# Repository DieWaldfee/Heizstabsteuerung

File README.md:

# Heizstabsteuerung

Heizstabsteuerung (Platine und Software) zur Ansteuerung eines Heizstabs in einem Pufferspeicher (Heizung)

**zugehörige Repositories**<br>

- PowerGuard (Steuerungsplatine <a href="https://github.com/DieWaldfee/PowerGuard"> Link </a>)
- Heizstabsteuerung (dieses Repository)
- Heizstab_ioBroker (Ansteuerungs-Blockly - ein MQTT-Broker wird benötigt - Link)

**Funktion:** <br>
Der ESP32 steuert 3 Temperatursensoren (DS18B20) an und liest diese aus. Zwei der Sensoren sollen am Referenzpunkt der Heizungsanlage (an Pufferspeichers der Heizung) angebracht werden, in dem auch der elektrische Heizstab eingeschraubt ist.
Die beiden Werte werden einerseits verglichen und andererseits benutzt, um die Pufferspeichertemperatur zu überwachen. Liegt die Temperatur zu hoch, dann ist zu viel Energie im Pufferspeicher und vermutlich ist der Heizstab dafür ursächlich -> der Heizstabsteuerung abgeschaltet (L1, L2, L3)und damit in den sicheren Zustand überführt.<p>
Liegt die Temperatur der beiden Sensoren über der eingestellten, kritischen Temperatur, so schaltet sich der ESP32 ganz ab und meldet dies optisch über die rote LED. Die Standardschaltung erfolgt über die beiden Sensoren. Eine Fehlerabschaltung erfolgt auch, wenn die Werte der Sensoren zu stark differieren (float deltaT = 2.0;).
Der dritte Sensor wird am höchsten Punkt des Pufferspeichers angebracht und dient der Überwachung der maximal zulässigen Puffertemperatur. Der Sensorwert wird zur Notabschaltung des ESP verwendet, sollte der Puffer signifikat zu heiß werden.
Die Kommunikation mit dem ESP32 wird über WiFi abgewickelt und über das Protokoll MQTT umgesetzt. Es stehen mehrere Befehle zur Verfügung, die ebenfalls via MQTT an den ESP gesendet werden kann. Neben "restart" (führt zu einem Neutstart des ESP32) kann die ganze Konfiguration un der debug-Level angepasst werden. Alle Anpassungen sind nach einem Neustart verlohren, da diese nicht permanet gespeichter werden (aber neue Parameter flashen geht ja fix). Befehle werden unter der MQTT-Hierarchie in folgendem Ort empfangen: "SmartHome/Keller/Heizung/ESP32_Heizstabsteuerung/command" (MQTT_SERIAL_RECEIVER_COMMAND)

**Hardwarevarianten:** <br>
Das Programm unterstützt zwei Hardwarevarianten in einem gemeinsamen Code. Die Auswahl erfolgt über den Parameter `HARDWARE_VERSION` in `src/secrets.h`:

- `HARDWARE_VERSION 1` → V1.0 Lochrasterplatine (OK-LED + ERROR-LED)
- `HARDWARE_VERSION 2` → V2.0 Platinenversion/PCB (OK-LED + MSG-LED + ERROR-LED)

**Entwicklungsumgebungen:** <br>
Die Software für den ESP32 wird mit **PlatformIO** (VSCode-Extension) entwickelt. Compile und Flash sind per Knopfdruck oder über `pio run --target upload` möglich. Die Installation ist sehr einfach und im Netz gut dokumentiert.<br>
Die Platine (PCB) habe ich in Eagle von AutoCAD modelliert. Für Maker gibt es eine kostenfreie Version. Die CAM-Daten (PCB-Produktionsdaten), sowie die BOM (Stückliste) sind ebenfalls aus Eagle ausgegeben.
Eine Übersichtsversion der Platine ist mit Fritzing umgesetzt und enthält auch einige Notizen zur Pinbelegung.<br>

**benötigte Umgebung:** <br>

- ioBroker zur Ansteuerung (geht natürlich auch mit anderen SmartHome-Systemen, solange diese MQTT sprechen können)
- ioBroker MGTT-Adapter
- MQTT-Broker: z.B. mosquitto unter Linux/Debian/Raspian...
- 230V Stromversorgung oder alternativ eine 5V Versorgung über z.B. ein USB-Ladegerät (muss 2 ESP32 sicher versorgen können -> 2A reicht völlig aus) oder über die Schraubklemmen anderweitig versorgt.

### Abhängigkeiten (PlatformIO – platformio.ini):

| Header                | Bibliothek                                                                                                  |
| --------------------- | ----------------------------------------------------------------------------------------------------------- |
| `OneWire.h`           | OneWire git-master (v2.3.7 inkompatibel mit ESP-IDF 5.x; v2.3.8 hat einen Bug – git-master enthält den Fix) |
| `DallasTemperature.h` | DallasTemperature by Miles Burton v4.0.4                                                                    |
| `WiFi.h`              | Arduino / ESP32-Framework                                                                                   |
| `WiFiClient.h`        | Arduino / ESP32-Framework                                                                                   |
| `PubSubClient.h`      | PubSubClient by Nick O'Leary v2.8                                                                           |
| `Wire.h`              | Arduino / ESP32-Framework                                                                                   |
| `LiquidCrystal_I2C.h` | LiquidCrystal_I2C by Frank de Brabander ^1.1.0                                                              |
| `EmonLib.h`           | EmonLib-esp32 – ESP32-optimierter Fork                                                                      |
| `esp_task_wdt.h`      | Espressif Framework                                                                                         |

### Board ESP32

Platform: `https://github.com/pioarduino/platform-espressif32` (Release 55.03.38-1)<br>
Board: `esp32dev`, Framework: `arduino`<br>

**aktuelle Versionen:** <br>

- ESP-Software V2.0.2
- PCB (Eagle) V2.0.1
- CAM V1.0
- BOM V2.0
- Fritzing V2.0

Die PCB V2.x ist für einen Platinenhersteller konstruiert => CAM-files können einfach der Bestellung beigefügt werden (z.B. bei https://jlcpcb.com für 2$ 5St Stand 11.11.2023) und ein paar Tage später ist die Platine fertig..
In der BOM findet sich die Stückliste für die Bestückung wieder.

Zugehöriges Projekt: https://github.com/users/DieWaldfee/projects/1

**Installation:**

- `src/secrets.h.example` nach `src/secrets.h` kopieren und eigene Zugangsdaten eintragen:<br>
  &nbsp;&nbsp;&nbsp;– WLAN-SSID, WLAN-Passwort, Hostname<br>
  &nbsp;&nbsp;&nbsp;– MQTT-Broker (IP, Port, User, Passwort)<br>
  &nbsp;&nbsp;&nbsp;– Hardwarevariante: `HARDWARE_VERSION 1` (Lochraster) oder `HARDWARE_VERSION 2` (Platine)<br>
  &nbsp;&nbsp;&nbsp;
- MQTT-Pfade sind in `src/Heizstabsteuerung.cpp` als `#define` hinterlegt und müssen in der Regel nicht geändert werden. <br>
  &nbsp;&nbsp;&nbsp;
- Adressen der DS18B20-Sensoren ermitteln und in `src/Heizstabsteuerung.cpp` eintragen. Hierzu muss der Debuglevel auf 1 gestellt werden (MQTT-Befehl `debug=1`) und die Ausgabe im Serial Monitor beobachtet werden. OnStart gibt der ESP32 die Sensoradressen aus.<br>
  &nbsp;&nbsp;&nbsp;
- Kalibrierung der Stromsensoren: Hierzu das separate Projekt **STC013_cal** (Sternverschaltung) bzw. **STC013_Dreieck_cal** (Dreiecksverschaltung) verwenden (siehe Abschnitt _Nachträgliche Kalibrierung_). <br>
  &nbsp;&nbsp;&nbsp;
- Bei Fehlern kann per MQTT-Befehl `debug=<0-3>` der Debug-Level für die Ausgaben auf den Serial Monitor eingestellt werden: 0 = BootUp only; 1 = Basic; 2 = Advanced; 3 = Absolut
- ESP-Software wird über PlatformIO auf das "ESP32 Dev Kit" compiliert und übertragen.
- Platine entweder via Eagle an PCB-Hersteller übermitteln oder mit einer Lochrasterplatine per Hand aufbauen.
- Platine bestücken + ESP und Level-Shifter (3.3V <-> 5V) aufsetzen.
- Relais anschließen.
- 12V Versorgung der Heizstabsteuerung wird über LED-Treiber realisiert.

**Displayinhalte:**

- Zeile 1;
  - L1 => Leiter 1 / Phase 1
  - L2 => Leiter 2 / Phase 2
  - L3 => Leiter 3 / Phase 3
  - hinter Lx: "-" => nicht geschaltet; "\*" => geschaltet
  - hinter Schaltzustand: "-" => ungeprüft; "x" => Fehler zwischen Strommessung und Soll-Schaltzustand; ":heavy_check_mark:" => Strommessung korrekt vs. Sollschaltzustand geprüft
  - hinter dem Block L3 folgt das Symbol für den Lüfterzustand: " " => Lüfter nicht geschaltet; ">>Lüftersymbol<<" => Lüfter geschaltet
  - hinter dem Lüftersymbol folgt MQTT-Symbol: " " => kein MQTT-Verbindung gegeben; "<<Wifi-Symbol>>" => MQTT-Verbingung aktiv
    Zeile 2:
  - T_Top: Temperatursensor am obersten Messpunkt - dient der Safety, um nicht zu überhitzen [°C]
  - T_Messpunkt_1: erste Messung auf der Entschiedungsebene (in der Regel parallel zum Sensor der Heizung) [°C]
  - T_Messpunkt_2: zweite Messung auf der Entschiedungsebene [°C]

**Steuerung:**

- Befehle werden über MQTT auf `/command` gesendet (Topic: `SmartHome/Keller/Heizung/ESP32_Heizstabsteuerung/command`).
- Befehlsliste (alle Befehle liegen in der MQTT-Callback-Funktion `void mqttCallback(...)`):
  - "L1 ein": schaltet L1 ein
  - "L1 aus": schaltet L1 aus
  - "L2 ein": schaltet L2 ein
  - "L2 aus": schaltet L2 aus
  - "L3 ein": schaltet L3 ein
  - "L3 aus": schaltet L3 aus
  - "L12 ein": schaltet L1 und L2 ein
  - "L12 aus": schaltet L1 und L2 aus
  - "L13 ein": schaltet L1 und L3 ein
  - "L13 aus": schaltet L1 und L3 aus
  - "L23 ein": schaltet L2 und L3 ein
  - "L23 aus": schaltet L2 und L3 aus
  - "L123 ein": schaltet L1, L2 und L3 ein
  - "L123 aus": schaltet L1, L2 und L3 aus
  - "Fan ein" / "Fan aus": schaltet den Lüfter ein/aus
  - "IrmsOn": startet die Stromsensor-Auswertung (befüllt Irms11/21/31 – Phase ein)
  - "IrmsOff": startet die Stromsensor-Auswertung (befüllt Irms10/20/30 – Phase aus)
  - "debug=\<0-3\>": setzt den Debug-Level (0=BootUp only; 1=Basic; 2=Advanced; 3=Absolut)
  - "panicMode=0": setzt den panicMode zurück
  - "thermalError=0" / "thermalError=1": setzt thermalError
  - "thermalLimit=0" / "thermalLimit=1": setzt thermalLimit
  - "checkError=0" / "checkError=1": setzt checkError
  - "ErrorLED aus": quittiert die Fehler-LED
  - "restart" / "reboot": führt zu einem Neustart des ESP32

**Nachträgliche Kalibrierung der Strommessung:**

Die SCT-013-Stromsensoren müssen für eine genaue Leistungsmessung individuell kalibriert werden, da ADC-Eingangswiderstände und Sensorexemplare streuen. Für die Kalibrierung stehen zwei separate PlatformIO-Projekte bereit — je nach Verschaltung des Heizstabs.

**Voraussetzungen:**

- Zangenampermeter zur Referenzmessung an allen drei Phasen
- Serieller Monitor (115200 Baud)
- Der Heizstab muss während der Lastmessung vollständig betriebsbereit angeschlossen sein

---

**Sternverschaltung — `STC013_cal` / `STC013_cal.cpp`**

Bei einem sternverschalteten Heizstab trägt jede Phase eine unabhängige Wicklung. Die Phasen werden nacheinander einzeln zugeschaltet.

Ablauf:

1. Referenzwerte mit dem Zangenampermeter unter Last an L1, L2 und L3 messen.
2. Die gemessenen Ströme in den Variablen `Irms_L1_xA`, `Irms_L2_xA`, `Irms_L3_xA` eintragen.
3. Sketch flashen und seriellen Monitor öffnen.

Der Sketch führt für jede Phase automatisch zwei Messreihen durch:

- **Nullmessung** (Last aus): 10 Messungen ohne Strom; die ersten 3 werden verworfen. Der Mittelwert der verbleibenden 7 Messungen ergibt den empfohlenen neuen Wert für `ADC_LX_zeroCorr`. Dieser Offset korrigiert den Leckstrom des Sensors im stromlosen Zustand.
- **Lastmessung** (Last ein): Das zugehörige SSR wird zugeschaltet. Aus dem Mittelwert der 7 gültigen Messungen und dem Referenzwert vom Zangenampermeter berechnet der Sketch den neuen `ADC_LX_corr`-Faktor nach der Formel:

```
ADC_LX_corr_neu = (Irms_Referenz / Irms_gemessen) * ADC_LX_corr_alt
```

4\. Die ausgegebenen Korrekturwerte für `ADC_LX_corr` und `ADC_LX_zeroCorr` in `src/Heizstabsteuerung.cpp` übernehmen und neu flashen.

Der `loop()` wiederholt die gesamte Messreihe automatisch, sodass mehrere Durchläufe für eine stabile Mittelung genutzt werden können.

---

**Dreiecksverschaltung — `STC013_Dreieck_cal` / `STC013_Dreieck_cal.cpp`**

Bei einem dreiecksverschalteten Heizstab fließen die Strangströme durch die Wicklungen zwischen den Phasen. Die Kalibrierung erfolgt stufenweise, weil sich der Laststrom in L3 erst bei Stufe 2 (alle drei Phasen aktiv) vollständig ausbildet.

Schaltstufen:

| Stufe | Aktive Phasen | Beschreibung                            |
| ----- | ------------- | --------------------------------------- |
| 1     | L1 + L2       | Eine Dreieckwicklung zwischen L1 und L2 |
| 2     | L1 + L2 + L3  | Alle drei Wicklungen aktiv              |

Ablauf:

1. Referenzwerte mit dem Zangenampermeter messen:
   - L1 und L2 in **Stufe 1** (nur L1 + L2 eingeschaltet)
   - L3 in **Stufe 2** (alle drei Phasen eingeschaltet)
2. Werte eintragen: `Irms_L1_xA` und `Irms_L2_xA` für Stufe 1, `Irms_L3_xA` für Stufe 2.
3. Sketch flashen und seriellen Monitor öffnen.

Der Sketch führt zunächst Nullmessungen für alle drei Sensoren durch (alle Phasen aus), dann:

- **Stufe 1**: L1 und L2 werden zugeschaltet — Kalibrierung von `ADC_L1_corr` und `ADC_L2_corr`
- **Stufe 2**: L3 wird zusätzlich zugeschaltet — Kalibrierung von `ADC_L3_corr`

Auch hier werden je 10 Messungen durchgeführt, die ersten 3 verworfen und aus den verbleibenden 7 der Mittelwert gebildet. Die Korrekturformel ist identisch zur Sternverschaltung.

4\. Die ausgegebenen Korrekturwerte für `ADC_LX_corr` und `ADC_LX_zeroCorr` in `src/Heizstabsteuerung.cpp` übernehmen und neu flashen.

---

**Kalibrierparameter in `src/Heizstabsteuerung.cpp`:**

| Parameter                                                 | Bedeutung                                            |
| --------------------------------------------------------- | ---------------------------------------------------- |
| `ADC_L1_corr` / `ADC_L2_corr` / `ADC_L3_corr`             | Skalierungsfaktor für EmonLib (Rohwert → Ampere)     |
| `ADC_L1_zeroCorr` / `ADC_L2_zeroCorr` / `ADC_L3_zeroCorr` | Offset-Korrektur für Leckstrom bei stromlosem Sensor |

---

Alternativ kann die manuelle Methode über MQTT verwendet werden:

- Phasenlimits temporär erhöhen: `phasen1Limit=100`
- Phasen ausschalten: `L123 aus`, dann `IrmsOff` → Irms10/20/30 werden befüllt
- Phasen einschalten: `L123 ein`, dann `IrmsOn` → Irms11/21/31 werden befüllt
- Tatsächlichen Strom parallel mit Zangenampermeter messen
- Korrekturwerte berechnen: ADC_L1_corr = Asoll/Aist × 15A
- Phasen ausschalten: `L123 aus`, dann `reboot`

**Bezugsquellen:**

- Platinennetzteil AC-05-3 <a href="https://www.azdelivery.de/products/copy-of-220v-zu-5v-mini-netzteil"> AZ-Delivery </a>
- Levelshifter (3.3V <-> 5V) <a href="https://www.amazon.de/RUNCCI-YUN-Pegelwandler-Converter-BiDirektional-Mikrocontroller/dp/B082F6BSB5/ref=sr_1_2?__mk_de_DE=%C3%85M%C3%85%C5%BD%C3%95%C3%91&crid=45TPG8CUP9&keywords=level+shifter&qid=1699045033&sprefix=level+shifter%2Caps%2C103&sr=8-2"> Amazon </a>
- Relais <a href="https://www.amazon.de/gp/product/B0B5816YJ7/ref=ppx_yo_dt_b_search_asin_image?ie=UTF8&th=1"> Amazon </a> oder <a href="https://www.az-delivery.de/products/relais-modul"> AZ Delivery </a>
- SSR-40DA, Eingang 4-32VDC <a href="https://www.amazon.de/gp/product/B071HP9NJD/ref=ppx_yo_dt_b_search_asin_title?ie=UTF8&psc=1"> Amazon </a>
- 12V LED-Treiber als Schaltspannung der SSR-Relais <a href="https://www.amazon.de/gp/product/B082NLNCSB/ref=ppx_yo_dt_b_search_asin_image?ie=UTF8&psc=1"> Amazon </a>
- JST-Buchse <a href="https://www.amazon.de/gp/product/B0B2R99X99/ref=ppx_yo_dt_b_search_asin_title?ie=UTF8&psc=1"> Amazon </a>
- Klemmbuchse <a href="https://www.amazon.de/gp/product/B087RN8FDZ/ref=ppx_yo_dt_b_search_asin_title?ie=UTF8&th=1"> Amazon </a>
- Widerstände 4,7kOhm, 220 Ohm, 330 Ohm, Led grün und rot Amazon / eBay / Conrad...
- Temperatursensoren DS18B20 <a href="https://www.az-delivery.de/products/2er-set-ds18b20-mit-3m-kabel"> AZ Delivery </a>
- Display 16x2 (I2C) <a href="https://www.az-delivery.de/products/bundlelcd-schnittstelle"> AZ Delivery </a>
- Sensor SCT013 (15A-Version) <a href="https://www.ebay.de/itm/401649505325?hash=item5d842d142d:g:qfcAAOSwt3hcBM4e&amdata=enc%3AAQAIAAAA0KgEqLPBwJ5v2dPxMSGkqbPdewVHlu9uy2CFB%2BhzhWl0xgc9madqMZlqcRs6Wc3fal3sByOXw4OTjDJD5ROsT7j0XoIEg7dg6DU4LENoYSTs2Lsc0dJQO4zoqct%2FeJhtZ5abkd7FmdelHZ%2B6X7udMPOxuFQvSkfjCg5lycrhV5p6hoq3ad6Px5PC0jifm43vGzVTaOA99K6uIJm%2BGWImFnsTzu5l855qGZi%2BdU%2B6e%2BG4HUboj3fOt6nB2IgD2IR6ODGIe1N4vzgpr%2FKM70GiCj4%3D%7Ctkp%3ABFBMuLykj_Ri"> eBay </a>

**fertige Steuerung:**

(Displayanzeige mit Schaltzustand der Phasen L1-L3, Lüfter, MQTT-Connect in der ersten Zeile. DIe zweite Zeile zeigt die Temperaturen Max am höchsten Punkt und den Sensor 1 und 2 am Relegungspunkt)

(bestückte Heizstabsteuerung mit angeschlossenen Strom-Sensoren und Display - ohne Temperatursensoren)

(bestückte Heizstabsteuerung mit angeschlossenen Strom-Sensoren und Display - ohne Temperatursensoren)

(Gesamtschaltung am Pufferspeicher - links die Steuerung und rechts die SSR-Relais und deren Kühlkörper)

**Haftungsausschluss**<br>
Deutsch: Dieses Projekt arbeitet mit Netzspannung (220 V) und darf ausschließlich von qualifiziertem Fachpersonal aufgebaut, installiert und betrieben werden. Durch die anliegende Spannung besteht Lebensgefahr! Fehler in Schaltung oder Software können zu Sachschäden (z. B. an Gebäude oder Heizung) oder zu gefährlichen Situationen für Leib und Leben führen. Nutzung auf eigene Gefahr – jegliche Haftung wird ausgeschlossen.
<br>
English: This project operates with mains voltage (220 V) and must only be assembled, installed, and operated by qualified professionals. The present voltage poses a risk of fatal electric shock! Errors in circuitry or software may cause property damage (e.g., to buildings or heating systems) or create life-threatening situations. Use at your own risk – any liability is disclaimed.

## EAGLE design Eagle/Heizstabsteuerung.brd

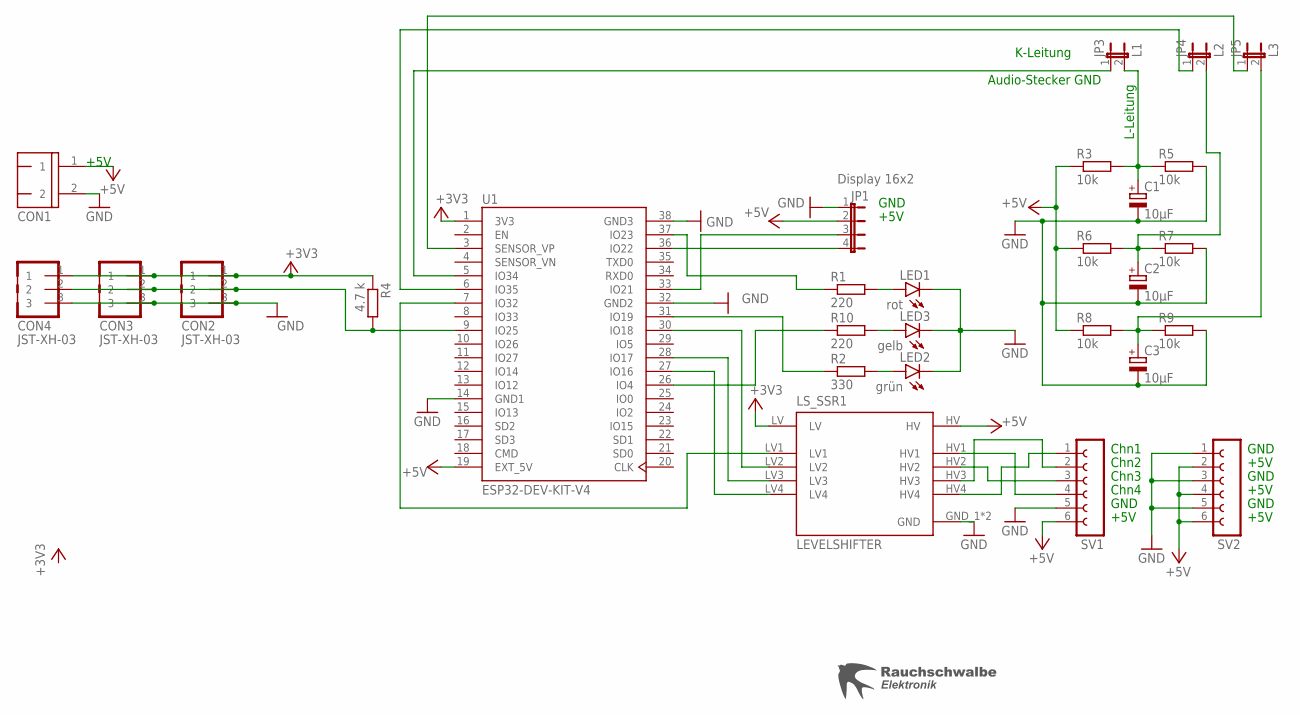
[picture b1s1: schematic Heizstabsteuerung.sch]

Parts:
C1, C2, C3: 10µF; E2,5-5
CON1: WAGO-500-2
CON2, CON3, CON4: JST-XH-03
JP1: Display 16x2; JP4
JP3: L1; JP1
JP4: L2; JP1
JP5: L3; JP1
LED1: rot; LED3MM
LED2: grün; LED3MM
LED3: gelb; LED3MM
LS_SSR1: LEVELSHIFTER
R1, R10: 220; 0207/10
R2: 330; 0207/10
R3, R5, R6, R7, R8, R9: 10k; 0207/10
R4: 4.7 k; 0207/10
SV1, SV2: FE06-1; FE06
U1: ESP32-DEV-KIT-V4
U$1: LOGO_RAUCHSCHWALBE

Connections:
+3V3: CON2.1, CON3.1, CON4.1, LS_SSR1.LV, R4.1, U1.1 (3V3)
+5V: CON1.1, JP1.2, LS_SSR1.HV, R3.1, R6.1, R8.1, SV1.6, SV2.2, SV2.4, SV2.6, U1.19 (EXT_5V)
GND: C1.-, C2.-, C3.-, CON1.2, CON2.3, CON3.3, CON4.3, JP1.1, LED1.K (C), LED2.K (C), LED3.K (C), LS_SSR1.GND_1 (GND), LS_SSR1.GND_2 (GND), R5.2, R7.2, R9.2, SV1.5, SV2.1, SV2.3, SV2.5, U1.14 (GND1), U1.32 (GND2), U1.38 (GND3)
unnamed: R1.1, U1.37 (IO23)
unnamed: C1.+, JP3.2, R3.2, R5.1
unnamed: LED3.A, R10.2
unnamed: JP1.3, U1.33 (IO21)
unnamed: JP1.4, U1.36 (IO22)
unnamed: R2.1, U1.31 (IO19)
unnamed: LED1.A, R1.2
unnamed: LED2.A, R2.2
unnamed: LS_SSR1.HV4, SV1.1
unnamed: LS_SSR1.LV1, U1.7 (IO32)
unnamed: CON2.2, CON3.2, CON4.2, R4.2, U1.9 (IO25)
unnamed: JP3.1, U1.5 (IO34)
unnamed: LS_SSR1.LV4, U1.27 (IO16)
unnamed: LS_SSR1.LV3, U1.28 (IO17)
unnamed: LS_SSR1.LV2, U1.30 (IO18)
unnamed: R10.1, U1.26 (IO4)
unnamed: LS_SSR1.HV1, SV1.4
unnamed: LS_SSR1.HV2, SV1.3
unnamed: LS_SSR1.HV3, SV1.2
unnamed: JP4.1, U1.6 (IO35)
unnamed: JP5.1, U1.3 (SENSOR_VP)
unnamed: C2.+, JP4.2, R6.2, R7.1
unnamed: C3.+, JP5.2, R8.2, R9.1

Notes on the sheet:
GND
+5V
Chn1
Chn2
Chn3
Chn4
K-Leitung
L-Leitung
Audio-Stecker GND

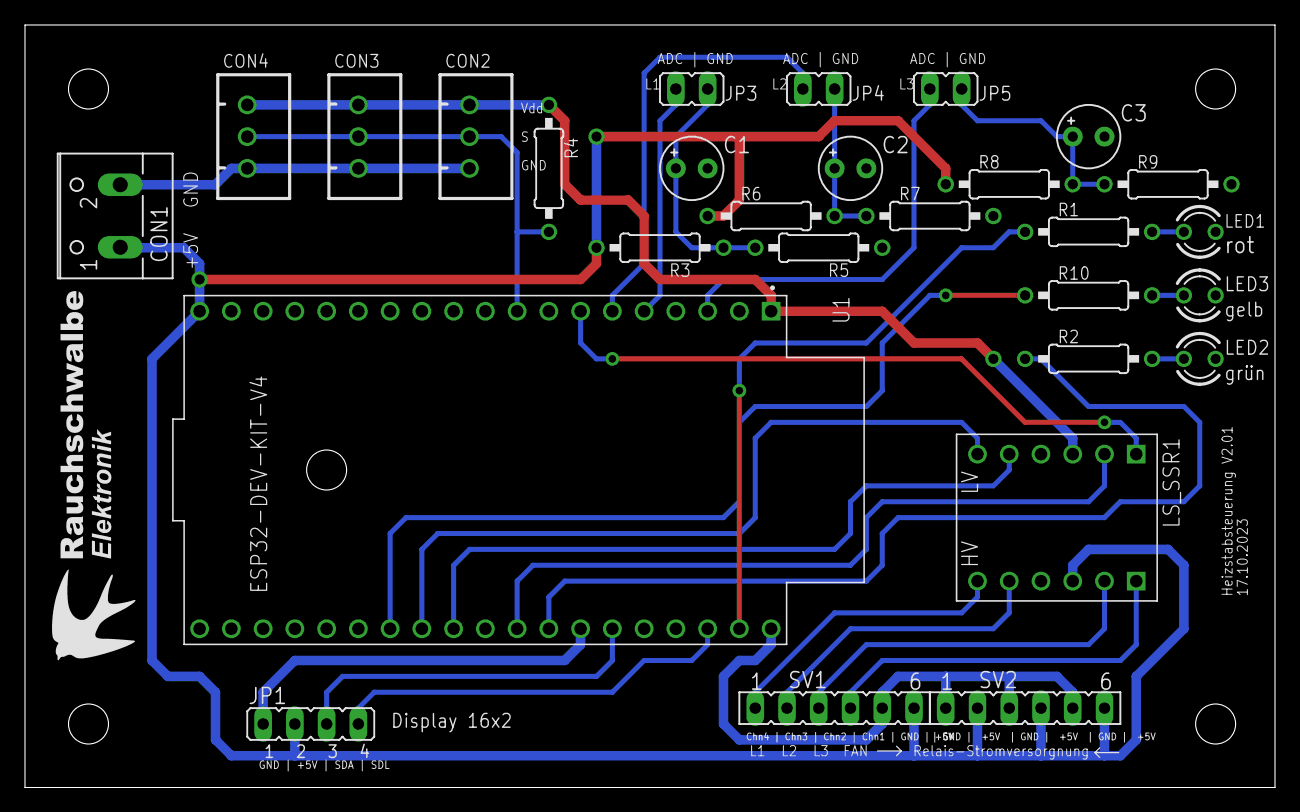
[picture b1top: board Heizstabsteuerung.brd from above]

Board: 2 copper layers, 100.0 x 61.0 mm, 29 parts (0 on the bottom side), 26 nets.

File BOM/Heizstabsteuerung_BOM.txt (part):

Stückliste exportiert aus C:/ESP32_Projekte/Heizstabsteuerung/Eagle/Heizstabsteuerung_V2.02.sch am 11.11.2023 21:42

Part    Value              Device             Package            Description                                         AVAILABILITY CHECK_PRICES                                                                     DESCRIPTION                                                MF                                                                                         MP                MPN           OC_FARNELL OC_NEWARK PACKAGE POPULARITY PRICE PURCHASE-URL                                           SNAPEDA_LINK SPICEPREFIX                                                                      
C1      10µF               CPOL-EUE2.5-5      E2,5-5             POLARIZED CAPACITOR, European symbol                                                                                                                                                                                                                                                                                                                                 16                                                                                   C                                                                                
C2      10µF               CPOL-EUE2.5-5      E2,5-5             POLARIZED CAPACITOR, European symbol                                                                                                                                                                                                                                                                                                                                 16                                                                                   C                                                                                
C3      10µF               CPOL-EUE2.5-5      E2,5-5             POLARIZED CAPACITOR, European symbol                                                                                                                                                                                                                                                                                                                                 16                                                                                   C                                                                                
CON1                       WAGO-500-2         WAGO-500-2         WAGO SCREW CLAMP                                                                                                                                                                                                                                                                                                          237-102       unknown    70K9898           32                                                                                                                                                                    
CON2    JST-XH-03          JST-XH-03          JST-XH-03                                                                                                                                                                                                                                                                                                                                                                                                                                                                                                                                                     
CON3    JST-XH-03          JST-XH-03          JST-XH-03                                                                                                                                                                                                                                                                                                                                                                                                                                                                                                                                                     
CON4    JST-XH-03          JST-XH-03          JST-XH-03                                                                                                                                                                                                                                                                                                                                                                                                                                                                                                                                                     
JP1     Display 16x2       JP4E               JP4                JUMPER                                                                                                                                                                                                                                                                                                                                                               15                                                                                                                                                                    
JP3     L1                 JP1E               JP1                JUMPER                                                                                                                                                                                                                                                                                                                                                               61                                                                                                                                                                    
JP4     L2                 JP1E               JP1                JUMPER                                                                                                                                                                                                                                                                                                                                                               61                                                                                                                                                                    
JP5     L3                 JP1E               JP1                JUMPER                                                                                                                                                                                                                                                                                                                                                               61                                                                                                                                                                    
LED1    rot                LED3MM             LED3MM             LED                                                                                                                                                                                                                                                                                                                                                                  97                                                                                                                                                                    
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
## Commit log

2023-11-05 ESP32-Programm V1.996 hinzugefügt
2023-11-05 Platine und Fritzing V1.996 ergänzt
2023-11-05 Readme erweitert
2023-11-05 Update README.md
    Sensoren und Kalibrierung ergänzt
2023-11-05 Update README.md
    fertige Schaltung in Bildern ergänzt
2023-11-11 Update V2.02 übertragen
2023-11-11 Update README.md
    Update auf PCB-Version V2.01
2023-11-11 Update README.md
    Bild hinzugefügt
2023-11-11 Update README.md
    Display und Informatíonsinhalt erläutert
2023-12-16 Update Heizstabsteuerung.ino
    looper mqttConnect vereinfacht
2023-12-16 Update Heizstabsteuerung.ino
    update
2023-12-16 Update Heizstabsteuerung.ino
    reboot an Wifi.Status = false optimiert
2024-05-20 V2.1.1
    Output TempSensor on Error (logLevel 3) + display optimization
2024-05-20 SCCT013 Kalibrierungsunterstützung
2024-05-21 V1.9.9_fix1
    Update improvements from V2.1.1
    - optimize Display messages
    - lastError send @ TempErrors
    BugFixes
2024-05-27 DS18B20 identify & test
2024-09-21 Add Wifi-Strength to MQTT -> V2.1.2
2024-09-21 separate secrets in file secrets.h
2024-09-22 add amps and Temps to lastError - opt. message
2024-09-24 V1.999_fix2
    Wifi Strength + additional Info via MQTT (Intregrety output + Thermal errors)
2024-09-28 Bugfix Deadlock -> V2.1.4
2024-09-28 Program migration from V2.1.4 -> 1.999_fix3
    Program migration from V2.1.4 -> 1.999_fix3
2024-09-29 V2.1.5
    fix assert problem with wdt
2024-09-29 V1.999_fix4
    angleichung an V2.1.5
    fix assert problems with wdt
2024-10-06 fix timing errors on DS18B20 & Integrety -> V2.1.6
    fixed possible timing errors while reading DS18B20 sensors
    fixed Integrety-errors when switching phases quickly
2024-10-06 fix display timing errors -> V2.1.7
    fixes display timing errors with reducing I2C speed from 400kH to 10kH
    (white screen or funny characters after operating over hours normaly)
2024-10-14 fix quick switches in integrety check -> V2.1.8
    fix quick switches in integrety check
2024-10-14 carry over from V2.1.8 -> fix 7
    carry over from V2.1.8 -> fix 7
2024-10-14 publish iobroker skripts - adapt please
    publish iobroker skripts - adapt please
2024-11-07 fix LCD Display and reboot problems
    -LCD refresh after 1000 cycles added
    -reboot after hardware problems added instead of dead lock.
2024-11-07 fix 8 according to V2.1.9
    -LCD refresh after 1000 cycles added
    -reboot after hardware problems added instead of dead lock.
2024-11-26 Update analog V2.1.10
    Update analog V2.1.10
    fix display errors - long time errors in LCD memory
2024-11-26 Update V2.1.10
    fix display errors on long run - memory errors in display accours => error in degree symbol or check symbol
2024-12-10 prevents reboot-message at iobroker-reboot
2025-01-14 fix automatic Reboot
    fix automatic Reboot
2025-05-29 V2.2.0 state modified; IP- and MAC-Adress in state
    V2.2.0 state modified; IP- and MAC-Adress in state
2025-05-29 analog V2.2.0
    Update analog V2.2.0
2025-07-26 info @debuglevel added
2025-07-26 analog V2.2.2
2025-07-27 command IrmsOn und IrmsOff integrated
    IrmsOn -> calibration routine to get core Irms values without correction
    IrmsOff -> get core Irms values at 0A
2025-07-27 analog v2.2.3
2025-07-29 Update Heizstabsteuerung.ino
    Kalibrierung angepasst
2025-08-16 direct return response on command
    direct update of the switched phase after check of the switching result
2025-09-08 ac-message after MQTT reconnect
    ac-message after MQTT reconnect to optimize startup script on iobroker
2025-09-08 ac-message after MQTT reconnect
    ac-message after MQTT reconnect to optimize startup scripts on iobroker
2025-09-08 ioBroker blockly scripts
    Setz of blockly scripts
    please change to your datapoints
2025-09-11 safe Reset: MQTT disconnected before ESP.restart
    safe Reset: MQTT disconnected before ESP.restart
    this avoids corrupt Data in MQTT from uncomplete messages
2025-09-11 analog V2.2.6
    MQTT disconnect before ESP.restart()
2025-09-12 MQTT rewritten as queued publishing task
    MQTT-communication queued and publishing via "MQTT sender task"
    This prevents publishing from multible tasks to one session
2025-09-12 analog V2.2.7
    MQTT publishing rewritten
2025-09-13 BugFix: watchdog definition added
2025-09-13 analog V2.2.8
    BugFix: Watchdog definition reintegrated
2026-04-20 Generell überarbeitet + Codeoptimierung
    - Generell überarbeitet
    - nach platformio / vscode übertragen
    - Codeoptimierung
    - Robustheit gegenüber race-conditions
2026-04-20 Delete ESP32DevKitV4/secrets.h
    outdated
2026-04-20 Delete ESP32DevKitV4/Heizstabsteuerung.ino
    outdated
2026-04-20 Delete ESP32DevKitV4/DS18B20_init/DS18B20_init.ino
    outdated
2026-04-20 Delete ESP32DevKitV4/SCT013_cal/Kalibrierung.xlsx
    outdated
2026-04-20 Delete ESP32DevKitV4/SCT013_cal/SCT013_cal_V2.ino.ino
    outdated
2026-04-20 Revise README for project details and dependencies
    Updated README.md to reflect changes in project details and dependencies.
2026-04-29 Spezifizierung für Sternschaltung
2026-04-29 Rename folder STC013_cal to STC013_Stern_cal
    Agent-Logs-Url: https://github.com/DieWaldfee/Heizstabsteuerung/sessions/2bf069a9-d2af-479c-a31b-7145fb28e255
2026-04-29 STC013_Dreieck_cal integriert
2026-04-29 Refactor secrets.h to use pragma once
    Removed preprocessor guards and added pragma once.
2026-04-29 Hardware ausgelagert
2026-04-29 Refactor DS18B20 sensor configuration and initialization
    Updated sensor address handling and configuration for DS18B20 temperature sensors. Removed unused definitions and improved initialization from hardware.h.
2026-04-29 Enhance SCT-013 calibration instructions in README
    Updated calibration instructions for SCT-013 current sensors, including separate projects for star and delta configurations. Added details on measurement procedures and parameters in the README.
